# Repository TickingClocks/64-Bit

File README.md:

# 64-Bit
Nixie Tube Clock driven by an STM32F446. Drives 6 IN-12 Nixie Tubes

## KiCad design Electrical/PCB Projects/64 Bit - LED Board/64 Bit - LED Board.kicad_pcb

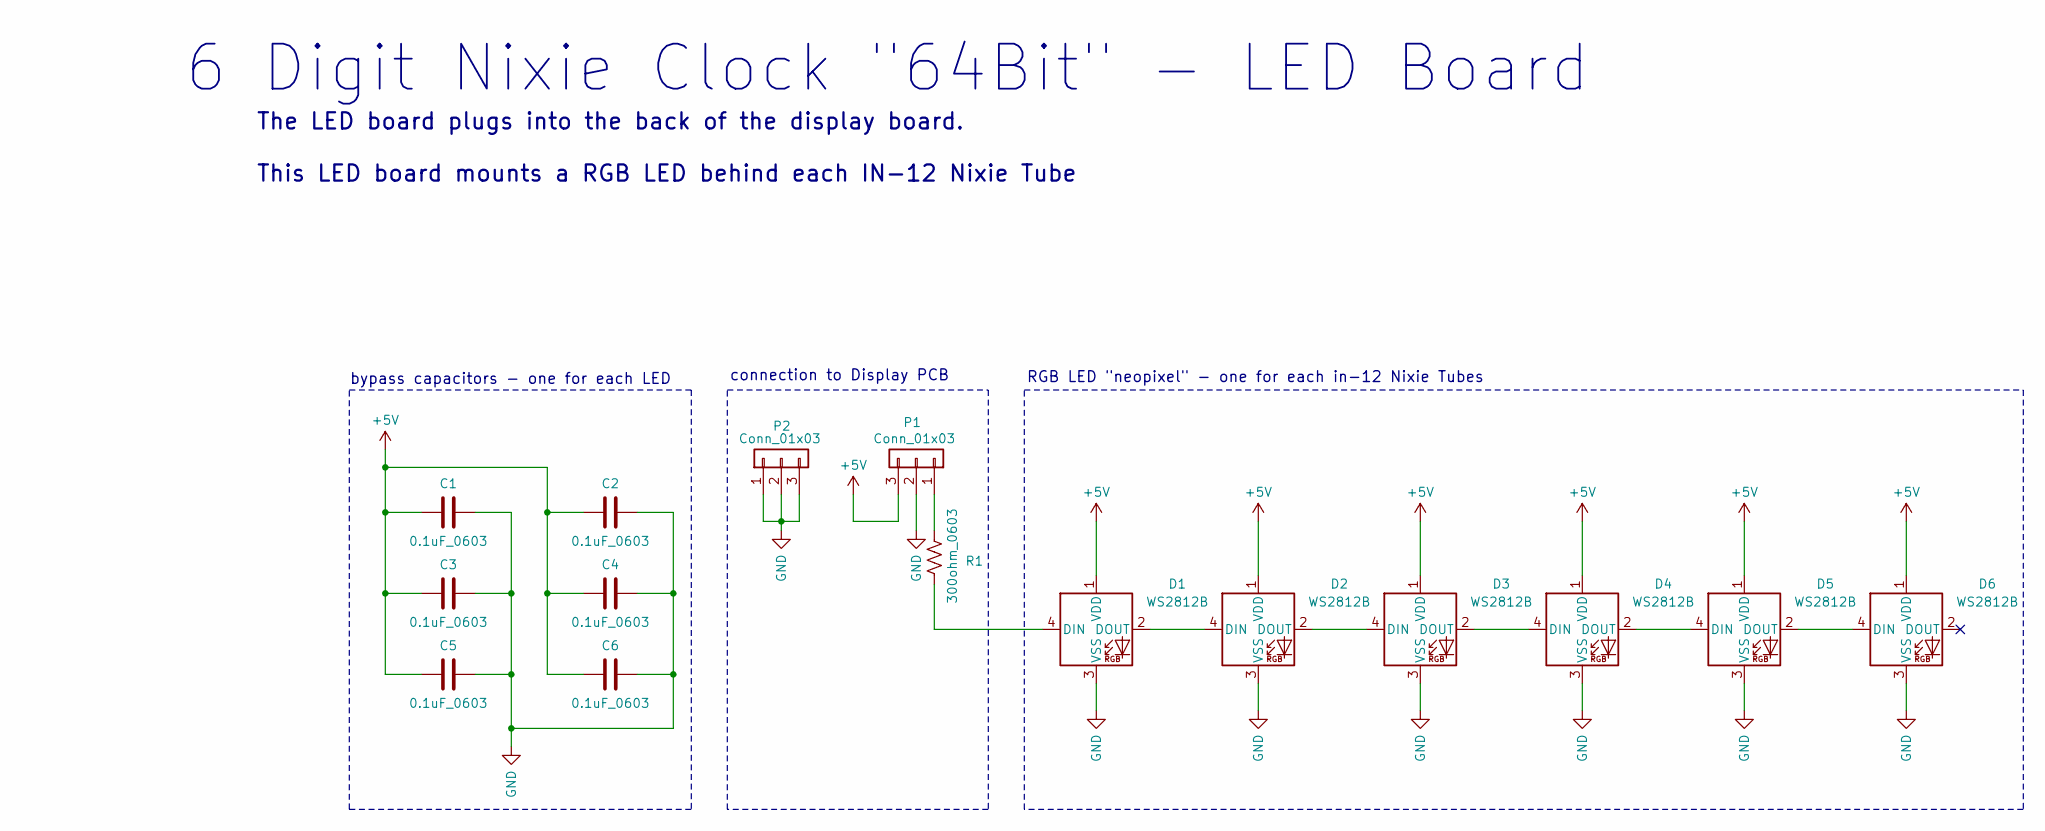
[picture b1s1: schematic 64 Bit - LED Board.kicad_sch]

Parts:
C1, C2, C3, C4, C5, C6: 0.1uF_0603; C_0603_1608Metric
D1, D2, D3, D4, D5, D6: WS2812B; LED_WS2812B_PLCC4_5.0x5.0mm_P3.2mm
P1, P2: Conn_01x03; PinHeader_1x03_P2.54mm_Vertical
R1: 300ohm_0603; R_0603_1608Metric

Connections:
+5V: C1.2, C2.2, C3.2, C4.2, C5.2, C6.2, D1.1 (VDD), D2.1 (VDD), D3.1 (VDD), D4.1 (VDD), D5.1 (VDD), D6.1 (VDD), P1.3
GND: C1.1, C2.1, C3.1, C4.1, C5.1, C6.1, D1.3 (VSS), D2.3 (VSS), D3.3 (VSS), D4.3 (VSS), D5.3 (VSS), D6.3 (VSS), P1.2, P2.1, P2.2, P2.3
unnamed: D1.4 (DIN), R1.2
unnamed: D1.2 (DOUT), D2.4 (DIN)
unnamed: D2.2 (DOUT), D3.4 (DIN)
unnamed: D3.2 (DOUT), D4.4 (DIN)
unnamed: D4.2 (DOUT), D5.4 (DIN)
unnamed: D5.2 (DOUT), D6.4 (DIN)
unnamed: P1.1, R1.1

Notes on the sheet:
connection to Display PCB
bypass capacitors - one for each LED
The LED board plugs into the back of the display board. This LED board mounts a RGB LED behind each IN-12 Nixie Tube
RGB LED "neopixel" - one for each in-12 Nixie Tubes
6 Digit Nixie Clock "64Bit" - LED Board

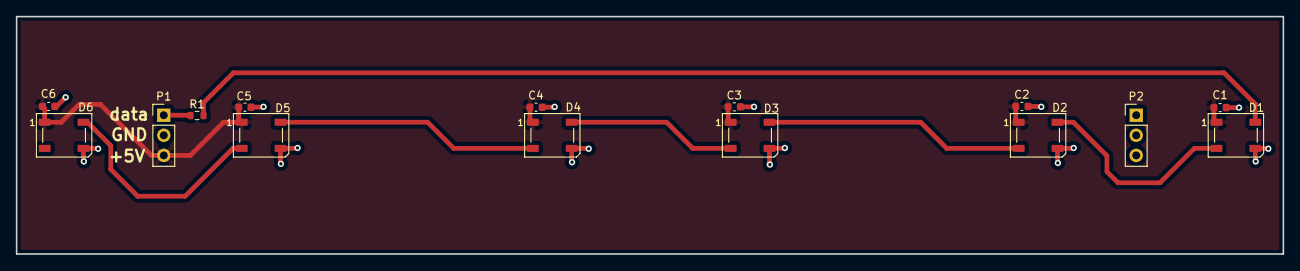
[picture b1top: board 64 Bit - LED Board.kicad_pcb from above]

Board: 2 copper layers, 160.1 x 30.0 mm, 15 parts (0 on the bottom side), 9 nets.

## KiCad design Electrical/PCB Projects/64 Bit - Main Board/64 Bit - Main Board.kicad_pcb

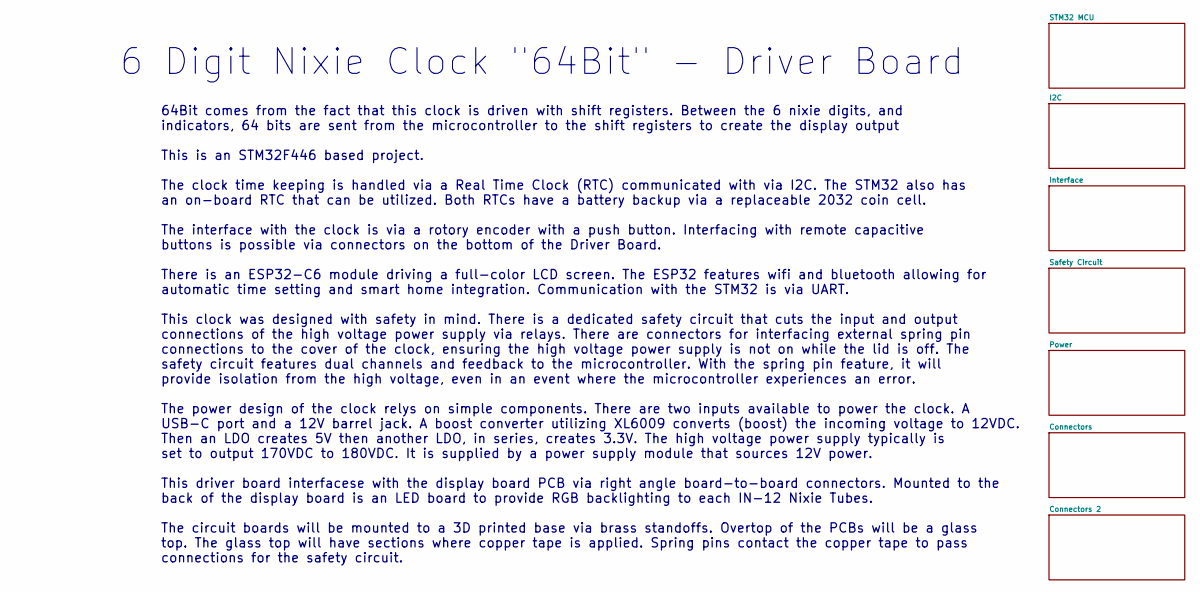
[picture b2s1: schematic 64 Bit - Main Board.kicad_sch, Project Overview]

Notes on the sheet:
64Bit comes from the fact that this clock is driven with shift registers. Between the 6 nixie digits, and indicators, 64 bits are sent from the microcontroller to the shift registers to create the display output This is an STM32F446 based project. The clock time keeping is handled via a Real Time C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
6 Digit Nixie Clock "64Bit" - Driver Board

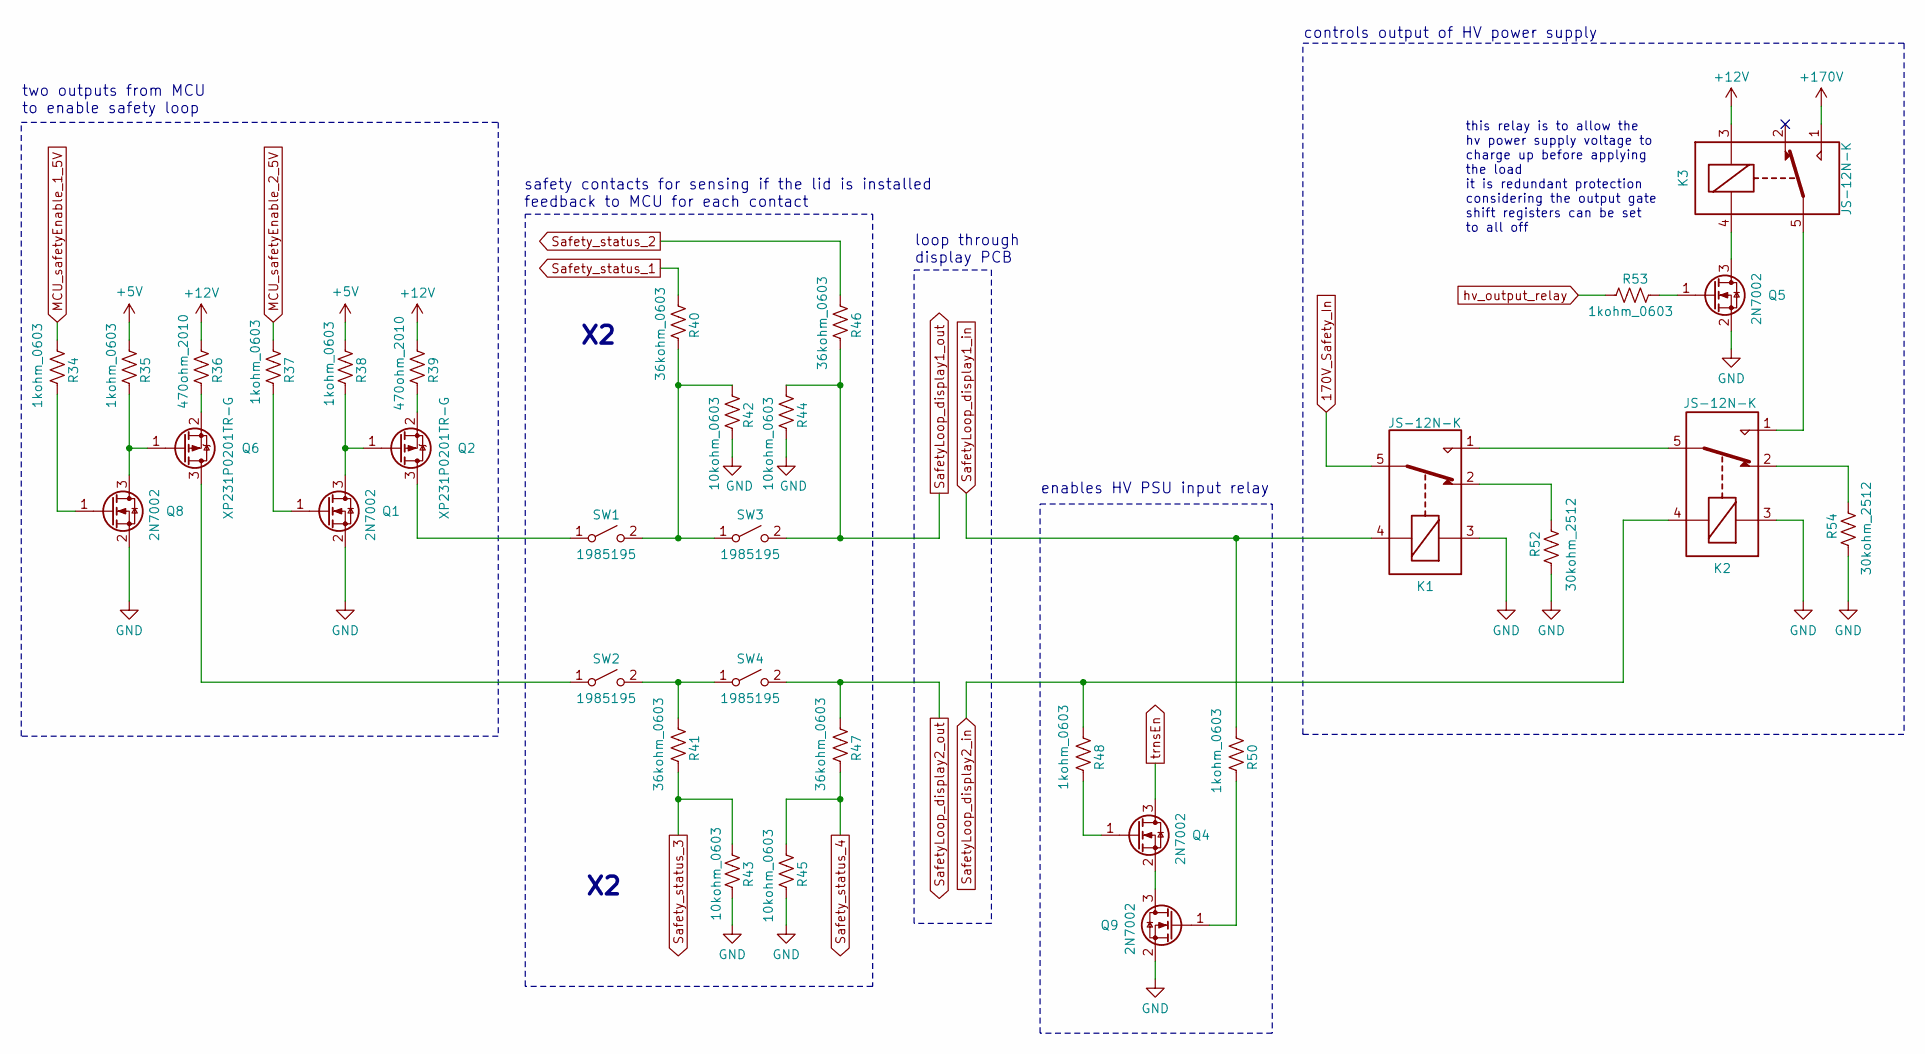
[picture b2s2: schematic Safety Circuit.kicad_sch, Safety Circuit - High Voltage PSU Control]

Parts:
K1, K2, K3: JS-12N-K
Q1, Q4, Q5, Q8, Q9: 2N7002; SOT-23
Q2, Q6: XP231P0201TR-G
R34, R35, R37, R38, R48, R50, R53: 1kohm_0603; R_0603_1608Metric
R36, R39: 470ohm_2010; R_2010_5025Metric
R40, R41, R46, R47: 36kohm_0603; R_0603_1608Metric
R42, R43, R44, R45: 10kohm_0603; R_0603_1608Metric
R52, R54: 30kohm_2512; R_2512_6332Metric
SW1, SW2, SW3, SW4: 1985195

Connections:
170V_Safety_In: K1.5; also elsewhere on the board
+5V: R35.2, R38.2; also elsewhere on the board
+12V: K3.3, R36.2, R39.2; also elsewhere on the board
+170V: K3.1; also elsewhere on the board
GND: K1.3, K2.3, Q1.2 (S), Q5.2 (S), Q8.2 (S), Q9.2 (S), R42.1, R43.1, R44.1, R45.1, R52.2, R54.2; also elsewhere on the board
MCU_safetyEnable_1_5V: R34.2; also elsewhere on the board
MCU_safetyEnable_2_5V: R37.2; also elsewhere on the board
unnamed: K1.1, K2.5
unnamed: K1.2, R52.1
unnamed: K2.1, K3.5
unnamed: K2.2, R54.1
unnamed: Q1.3 (D), Q2.1 (G), R38.1
unnamed: Q1.1 (G), R37.1
unnamed: Q2.3 (D), SW1.1 (A)
unnamed: Q2.2 (S), R39.1
unnamed: Q4.1 (G), R48.1
unnamed: Q4.2 (S), Q9.3 (D)
unnamed: K3.4, Q5.3 (D)
unnamed: Q5.1 (G), R53.1
unnamed: Q6.3 (D), SW2.1 (A)
unnamed: Q6.1 (G), Q8.3 (D), R35.1
unnamed: Q6.2 (S), R36.1
unnamed: Q8.1 (G), R34.1
unnamed: Q9.1 (G), R50.1
unnamed: R40.1, R42.2, SW1.2 (B), SW3.1 (A)
unnamed: R41.2, SW2.2 (B), SW4.1 (A)
SafetyLoop_display1_in: K1.4, R50.2; also elsewhere on the board
SafetyLoop_display1_out: R44.2, R46.1, SW3.2 (B); also elsewhere on the board
SafetyLoop_display2_in: K2.4, R48.2; also elsewhere on the board
SafetyLoop_display2_out: R47.2, SW4.2 (B); also elsewhere on the board
Safety_status_1: R40.2; also elsewhere on the board
Safety_status_2: R46.2; also elsewhere on the board
Safety_status_3: R41.1, R43.2; also elsewhere on the board
Safety_status_4: R45.2, R47.1; also elsewhere on the board
hv_output_relay: R53.2; also elsewhere on the board
trnsEn: Q4.3 (D); also elsewhere on the board

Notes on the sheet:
controls output of HV power supply
enables HV PSU input relay
loop through display PCB
this relay is to allow the hv power supply voltage to charge up before applying the load it is redundant protection considering the output gate shift registers can be set to all off
safety contacts for sensing if the lid is installed feedback to MCU for each contact
two outputs from MCU to enable safety loop

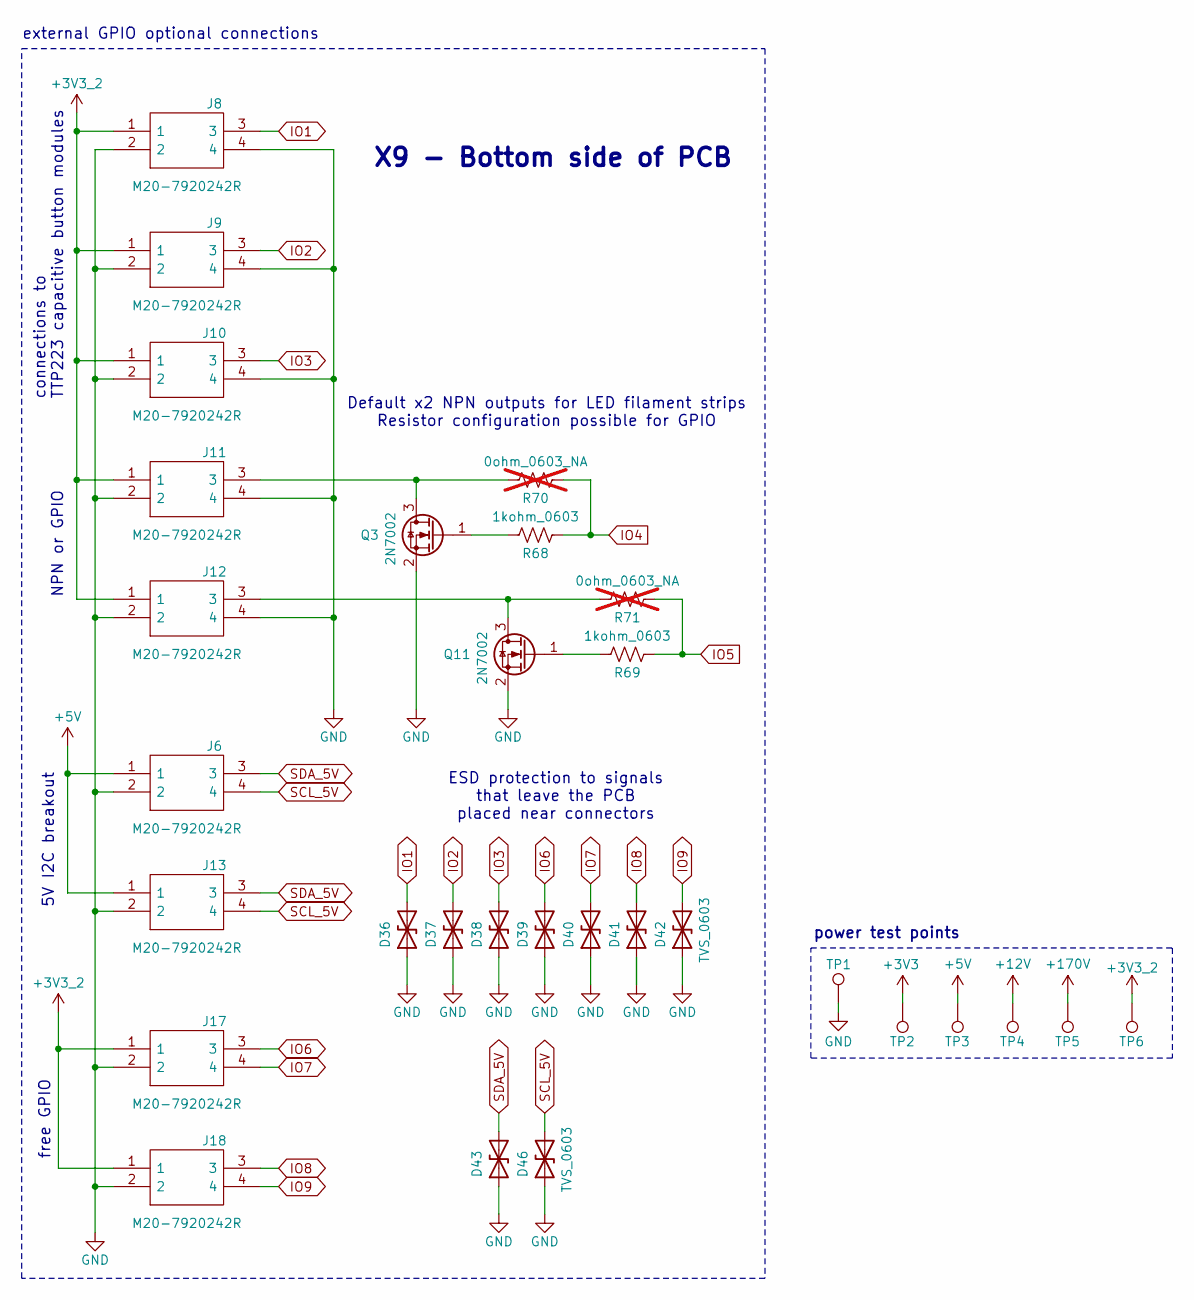
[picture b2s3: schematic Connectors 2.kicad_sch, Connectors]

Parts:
D36, D37, D38, D39, D40, D41, D42, D43, D46: TVS_0603; R_0603_1608Metric
J6, J8, J9, J10, J11, J12, J13, J17, J18: M20-7920242R; M207920242R; Mouser Part Number 855-M20-7920242R
Q3, Q11: 2N7002; SOT-23
R68, R69: 1kohm_0603; R_0603_1608Metric
R70, R71: 0ohm_0603_NA; R_0603_1608Metric; not fitted
TP1, TP2, TP3, TP4, TP5, TP6: TestPoint; TestPoint_THTPad_D1.5mm_Drill0.7mm

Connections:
+3V3: TP2.1; also elsewhere on the board
+3V3_2: J8.1, J9.1, J10.1, J11.1, J12.1, J17.1, J18.1, TP6.1; also elsewhere on the board
+5V: J6.1, J13.1, TP3.1; also elsewhere on the board
+12V: TP4.1; also elsewhere on the board
+170V: TP5.1; also elsewhere on the board
GND: D36.1 (A1), D37.1 (A1), D38.1 (A1), D39.1 (A1), D40.1 (A1), D41.1 (A1), D42.1 (A1), D43.1 (A1), D46.1 (A1), J6.2, J8.2, J8.4, J9.2, J9.4, J10.2, J10.4, J11.2, J11.4, J12.2, J12.4, J13.2, J17.2, J18.2, Q3.2 (S), Q11.2 (S), TP1.1; also elsewhere on the board
IO1: D36.2 (A2), J8.3; also elsewhere on the board
IO2: D37.2 (A2), J9.3; also elsewhere on the board
IO3: D38.2 (A2), J10.3; also elsewhere on the board
IO4: R68.1, R70.1; also elsewhere on the board
IO5: R69.1, R71.1; also elsewhere on the board
IO6: D39.2 (A2), J17.3; also elsewhere on the board
IO7: D40.2 (A2), J17.4; also elsewhere on the board
IO8: D41.2 (A2), J18.3; also elsewhere on the board
IO9: D42.2 (A2), J18.4; also elsewhere on the board
unnamed: J11.3, Q3.3 (D), R70.2
unnamed: Q3.1 (G), R68.2
unnamed: J12.3, Q11.3 (D), R71.2
unnamed: Q11.1 (G), R69.2
SCL_5V: D46.2 (A2), J6.4, J13.4; also elsewhere on the board
SDA_5V: D43.2 (A2), J6.3, J13.3; also elsewhere on the board

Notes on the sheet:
external GPIO optional connections
5V I2C breakout
ESD protection to signals that leave the PCB placed near connectors
NPN or GPIO
X9 - Bottom side of PCB
power test points
free GPIO
Default x2 NPN outputs for LED filament strips Resistor configuration possible for GPIO
connections to TTP223 capacitive button modules

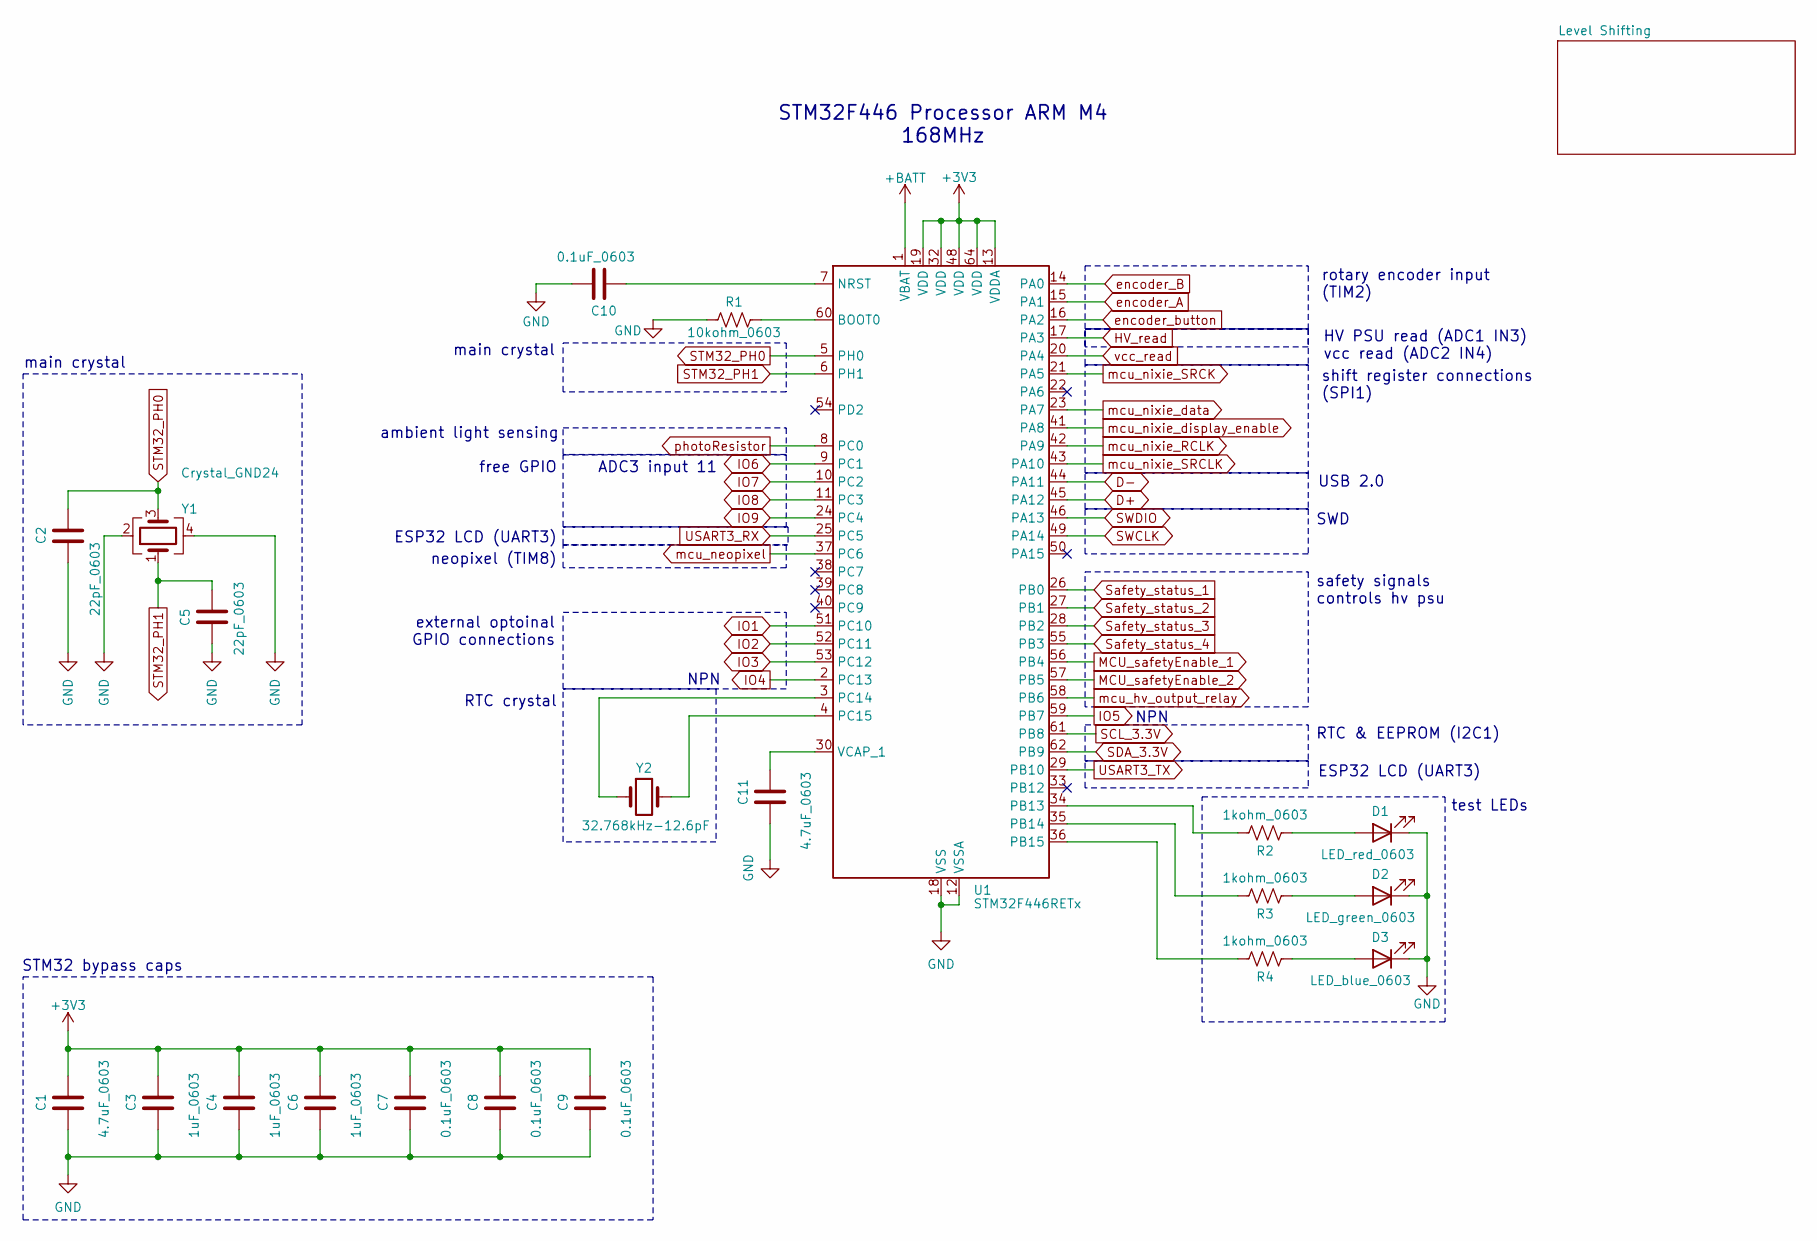
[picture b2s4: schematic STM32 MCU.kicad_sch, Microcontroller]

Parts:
C1, C11: 4.7uF_0603; C_0603_1608Metric
C2, C5: 22pF_0603; C_0603_1608Metric
C3, C4, C6: 1uF_0603; C_0603_1608Metric
C7, C8, C9, C10: 0.1uF_0603; C_0603_1608Metric
D1: LED_red_0603; LED_0603_1608Metric
D2: LED_green_0603; LED_0603_1608Metric
D3: LED_blue_0603; LED_0603_1608Metric
R1: 10kohm_0603; R_0603_1608Metric
R2, R3, R4: 1kohm_0603; R_0603_1608Metric
U1: STM32F446RETx; LQFP-64_10x10mm_P0.5mm
Y1: Crystal_GND24; ECS1602033TR3
Y2: 32.768kHz-12.6pF; 37.768kHz

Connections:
+3V3: C1.1, C3.1, C4.1, C6.1, C7.1, C8.1, C9.1, U1.13 (VDDA), U1.19 (VDD), U1.32 (VDD), U1.48 (VDD), U1.64 (VDD); also elsewhere on the board
+BATT: U1.1 (VBAT); also elsewhere on the board
D+: U1.45 (PA12); also elsewhere on the board
D-: U1.44 (PA11); also elsewhere on the board
GND: C1.2, C2.2, C3.2, C4.2, C5.1, C6.2, C7.2, C8.2, C9.2, C10.2, C11.2, D1.1 (K), D2.1 (K), D3.1 (K), R1.1, U1.12 (VSSA), U1.18 (VSS), U1.31 (VSS), U1.47 (VSS), U1.63 (VSS), Y1.2, Y1.4; also elsewhere on the board
HV_read: U1.17 (PA3); also elsewhere on the board
IO1: U1.51 (PC10); also elsewhere on the board
IO2: U1.52 (PC11); also elsewhere on the board
IO3: U1.53 (PC12); also elsewhere on the board
IO4: U1.2 (PC13); also elsewhere on the board
IO5: U1.59 (PB7); also elsewhere on the board
IO6: U1.9 (PC1); also elsewhere on the board
IO7: U1.10 (PC2); also elsewhere on the board
IO8: U1.11 (PC3); also elsewhere on the board
IO9: U1.24 (PC4); also elsewhere on the board
MCU_safetyEnable_1: U1.56 (PB4); also elsewhere on the board
MCU_safetyEnable_2: U1.57 (PB5); also elsewhere on the board
unnamed: D1.2 (A), R2.1
unnamed: D2.2 (A), R3.1
unnamed: D3.2 (A), R4.1
unnamed: R1.2, U1.60 (BOOT0)
unnamed: C10.1, U1.7 (NRST)
unnamed: R2.2, U1.34 (PB13)
unnamed: R3.2, U1.35 (PB14)
unnamed: R4.2, U1.36 (PB15)
unnamed: U1.3 (PC14), Y2.1
unnamed: U1.4 (PC15), Y2.2
unnamed: C11.1, U1.30 (VCAP_1)
SCL_3.3V: U1.61 (PB8); also elsewhere on the board
SDA_3.3V: U1.62 (PB9); also elsewhere on the board
STM32_PH0: C2.1, U1.5 (PH0), Y1.3
STM32_PH1: C5.2, U1.6 (PH1), Y1.1
SWCLK: U1.49 (PA14); also elsewhere on the board
SWDIO: U1.46 (PA13); also elsewhere on the board
Safety_status_1: U1.26 (PB0); also elsewhere on the board
Safety_status_2: U1.27 (PB1); also elsewhere on the board
Safety_status_3: U1.28 (PB2); also elsewhere on the board
Safety_status_4: U1.55 (PB3); also elsewhere on the board
USART3_RX: U1.25 (PC5); also elsewhere on the board
USART3_TX: U1.29 (PB10); also elsewhere on the board
encoder_A: U1.15 (PA1); also elsewhere on the board
encoder_B: U1.14 (PA0); also elsewhere on the board
encoder_button: U1.16 (PA2); also elsewhere on the board
mcu_hv_output_relay: U1.58 (PB6); also elsewhere on the board
mcu_neopixel: U1.37 (PC6); also elsewhere on the board
mcu_nixie_RCLK: U1.42 (PA9); also elsewhere on the board
mcu_nixie_SRCK: U1.21 (PA5); also elsewhere on the board
mcu_nixie_SRCLK: U1.43 (PA10); also elsewhere on the board
mcu_nixie_data: U1.23 (PA7); also elsewhere on the board
mcu_nixie_display_enable: U1.41 (PA8); also elsewhere on the board
photoResistor: U1.8 (PC0); also elsewhere on the board
vcc_read: U1.20 (PA4); also elsewhere on the board

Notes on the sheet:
HV PSU read (ADC1 IN3) vcc read (ADC2 IN4)
free GPIO
ESP32 LCD (UART3)
SWD
STM32 bypass caps
rotary encoder input (TIM2)
RTC & EEPROM (I2C1)
NPN
USB 2.0
external optoinal GPIO connections
test LEDs
ADC3 input 11
neopixel (TIM8)
safety signals controls hv psu
STM32F446 Processor ARM M4 168MHz
RTC crystal
shift register connections (SPI1)
ambient light sensing
main crystal

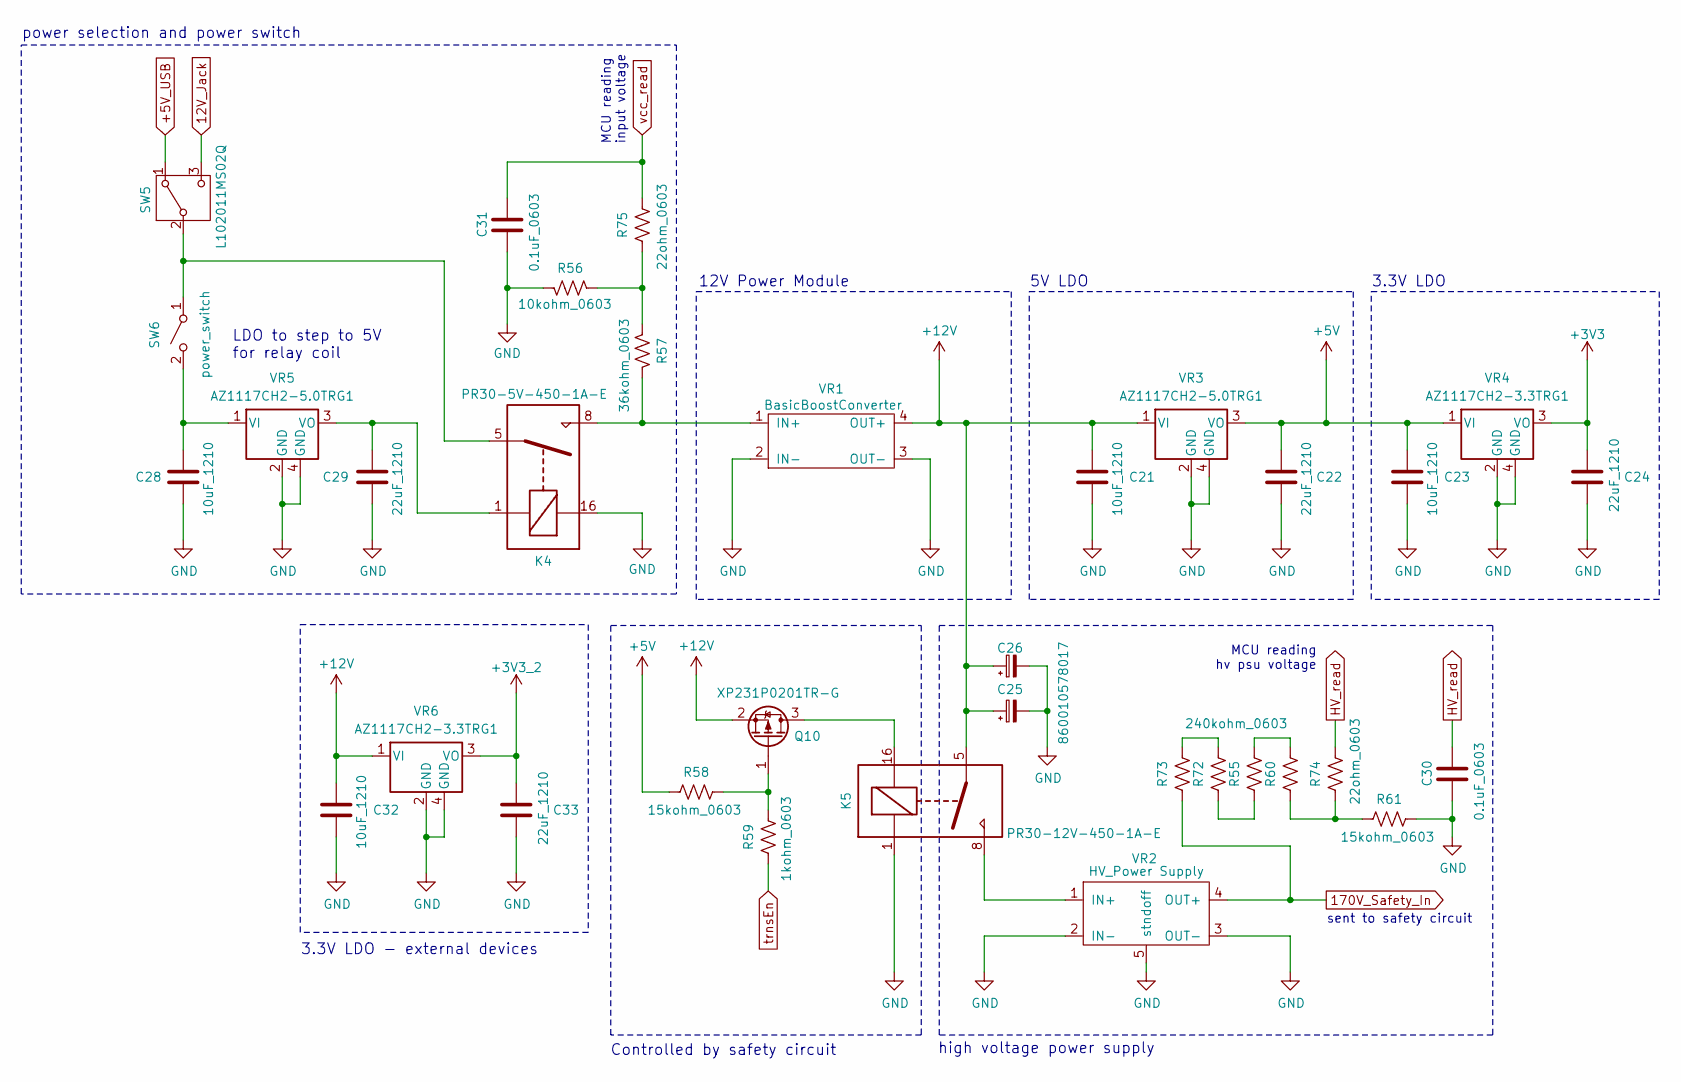
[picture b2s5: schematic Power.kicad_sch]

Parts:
C21, C23, C28, C32: 10uF_1210; C_1210_3225Metric
C22, C24, C29, C33: 22uF_1210; C_1210_3225Metric
C25, C26: 860010578017; CP_Radial_D13.0mm_P5.00mm
C30, C31: 0.1uF_0603; C_0603_1608Metric
K4: PR30-5V-450-1A-E; PR30-12V-450-1A-E
K5: PR30-12V-450-1A-E
Q10: XP231P0201TR-G
R55, R60, R72, R73: 240kohm_0603; R_0603_1608Metric
R56: 10kohm_0603; R_0603_1608Metric
R57: 36kohm_0603; R_0603_1608Metric
R58, R61: 15kohm_0603; R_0603_1608Metric
R59: 1kohm_0603; R_0603_1608Metric
R74, R75: 22ohm_0603; R_0603_1608Metric
SW5: L102011MS02Q
SW6: power_switch; 1985195
VR1: BasicBoostConverter; XL6009_Module(43mmx21mm)
VR2: HV_Power Supply; hv_psu
VR3, VR5: AZ1117CH2-5.0TRG1
VR4, VR6: AZ1117CH2-3.3TRG1

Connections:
12V_Jack: SW5.3 (C); also elsewhere on the board
170V_Safety_In: R73.1, VR2.4 (OUT+); also elsewhere on the board
+3V3: C24.1, VR4.3 (VO); also elsewhere on the board
+3V3_2: C33.1, VR6.3 (VO); also elsewhere on the board
+5V: C22.1, C23.1, R58.1, VR3.3 (VO), VR4.1 (VI); also elsewhere on the board
+5V_USB: SW5.1 (A); also elsewhere on the board
+12V: C21.1, C25.1, C26.1, C32.1, K5.5, Q10.2 (S), VR1.4 (OUT+), VR3.1 (VI), VR6.1 (VI); also elsewhere on the board
GND: C21.2, C22.2, C23.2, C24.2, C25.2, C26.2, C28.2, C29.2, C30.1, C31.1, C32.2, C33.2, K4.16, K5.1, R56.2, R61.2, VR1.2 (IN-), VR1.3 (OUT-), VR2.2 (IN-), VR2.3 (OUT-), VR2.5 (stndoff), VR3.2 (GND), VR3.4 (GND), VR4.2 (GND), VR4.4 (GND), VR5.2 (GND), VR5.4 (GND), VR6.2 (GND), VR6.4 (GND); also elsewhere on the board
HV_read: C30.2, R74.2; also elsewhere on the board
unnamed: K5.16, Q10.3 (D)
unnamed: Q10.1 (G), R58.2, R59.2
unnamed: R55.1, R72.1
unnamed: R55.2, R60.2
unnamed: R56.1, R57.2, R75.1
unnamed: R60.1, R61.1, R74.1
unnamed: R72.2, R73.2
unnamed: K4.5, SW5.2 (B), SW6.1 (A)
unnamed: C28.1, SW6.2 (B), VR5.1 (VI)
unnamed: K4.8, R57.1, VR1.1 (IN+)
unnamed: K5.8, VR2.1 (IN+)
unnamed: C29.1, K4.1, VR5.3 (VO)
trnsEn: R59.1; also elsewhere on the board
vcc_read: C31.2, R75.2; also elsewhere on the board

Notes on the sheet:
MCU reading input voltage
high voltage power supply
Controlled by safety circuit
5V LDO
sent to safety circuit
LDO to step to 5V for relay coil
3.3V LDO - external devices
12V Power Module
MCU reading hv psu voltage
power selection and power switch
3.3V LDO

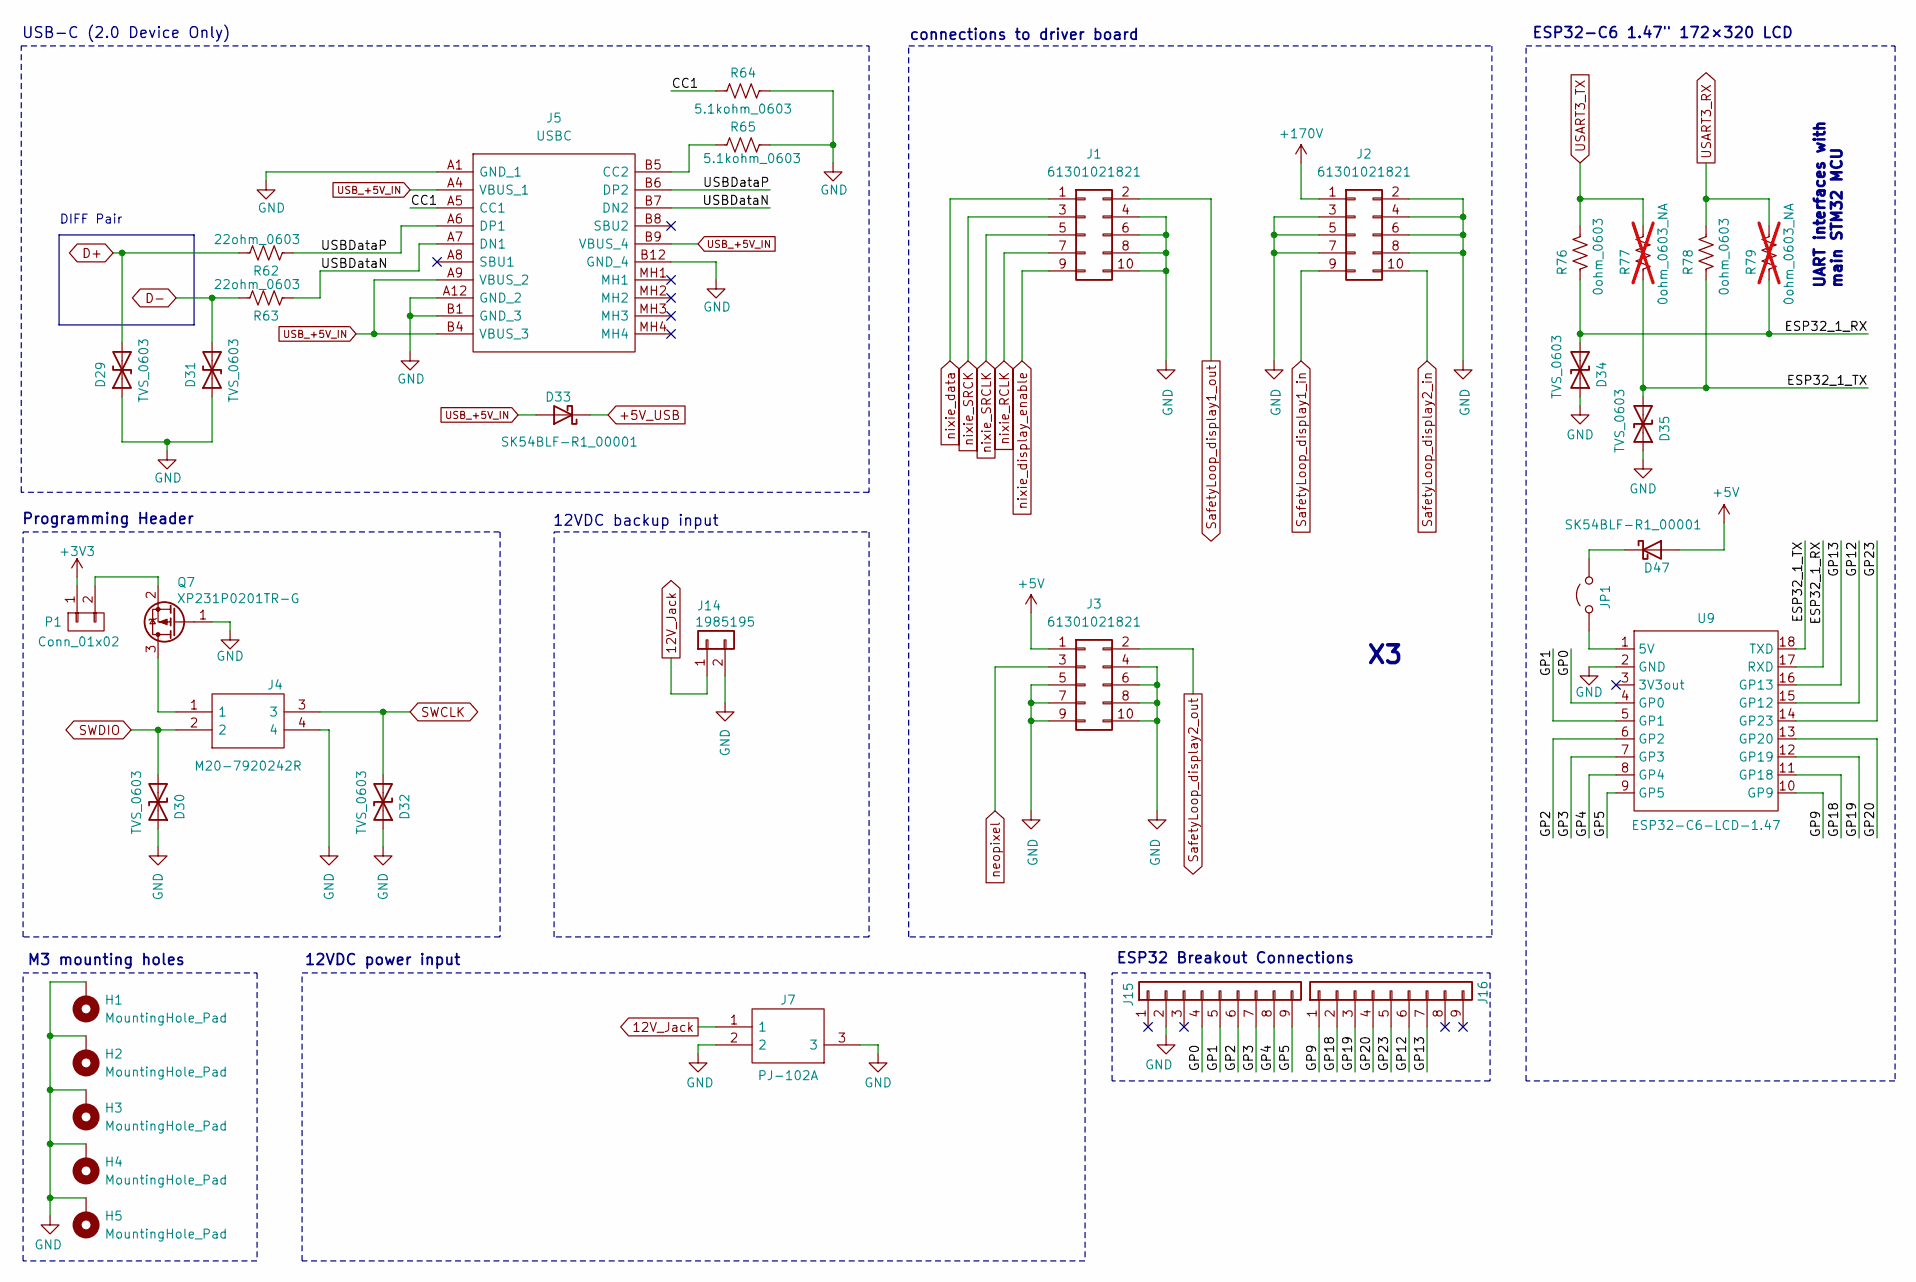
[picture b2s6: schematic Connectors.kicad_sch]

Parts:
D29, D30, D31, D32, D34, D35: TVS_0603; R_0603_1608Metric
D33, D47: SK54BLF-R1_00001
H1, H2, H3, H4, H5: MountingHole_Pad; M3 Standoff Footprint
J1, J2, J3: 61301021821
J4: M20-7920242R; M207920242R; Mouser Part Number 855-M20-7920242R
J5: USBC; USB421603A
J7: PJ-102A; PJ-102AH; Mouser Part Number 490-PJ-102A
J14: 1985195
J15, J16: Conn_01x09; PinSocket_1x09_P2.54mm_Vertical
JP1: Jumper_2_Open; PinHeader_1x02_P2.54mm_Vertical
P1: Conn_01x02; PinHeader_1x02_P2.54mm_Vertical
Q7: XP231P0201TR-G
R62, R63: 22ohm_0603; R_0603_1608Metric
R64, R65: 5.1kohm_0603; R_0603_1608Metric
R76, R78: 0ohm_0603; R_0603_1608Metric
R77, R79: 0ohm_0603_NA; R_0603_1608Metric; not fitted
U9: ESP32-C6-LCD-1.47

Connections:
12V_Jack: J7.1, J14.1; also elsewhere on the board
+3V3: P1.1; also elsewhere on the board
+5V: D47.2 (A), J3.1; also elsewhere on the board
+5V_USB: D33.1 (K); also elsewhere on the board
+170V: J2.1; also elsewhere on the board
/Connectors/CC1: J5.A5 (CC1), R64.2
/Connectors/ESP32_1_RX: D34.2 (A2), R76.1, R79.1, U9.17 (RXD)
/Connectors/ESP32_1_TX: D35.2 (A2), R77.1, R78.1, U9.18 (TXD)
/Connectors/GP0: J15.4, U9.4 (GP0)
/Connectors/GP1: J15.5, U9.5 (GP1)
/Connectors/GP2: J15.6, U9.6 (GP2)
/Connectors/GP3: J15.7, U9.7 (GP3)
/Connectors/GP4: J15.8, U9.8 (GP4)
/Connectors/GP5: J15.9, U9.9 (GP5)
/Connectors/GP9: J16.1, U9.10 (GP9)
/Connectors/GP12: J16.6, U9.15 (GP12)
/Connectors/GP13: J16.7, U9.16 (GP13)
/Connectors/GP18: J16.2, U9.11 (GP18)
/Connectors/GP19: J16.3, U9.12 (GP19)
/Connectors/GP20: J16.4, U9.13 (GP20)
/Connectors/GP23: J16.5, U9.14 (GP23)
/Connectors/USBDataN: J5.A7 (DN1), J5.B7 (DN2), R63.1
/Connectors/USBDataP: J5.A6 (DP1), J5.B6 (DP2), R62.1
D+: D29.2 (A2), R62.2; also elsewhere on the board
D-: D31.2 (A2), R63.2; also elsewhere on the board
GND: D29.1 (A1), D30.1 (A1), D31.1 (A1), D32.1 (A1), D34.1 (A1), D35.1 (A1), H1.1, H2.1, H3.1, H4.1, H5.1, J1.4, J1.6, J1.8, J1.10, J2.2, J2.3, J2.4, J2.5, J2.6, J2.7, J2.8, J3.4, J3.5, J3.6, J3.7, J3.8, J3.9, J3.10, J4.4, J5.A1 (GND_1), J5.A12 (GND_2), J5.B1 (GND_3), J5.B12 (GND_4), J7.2, J7.3, J14.2, J15.2, Q7.1 (G), R64.1, R65.2, U9.2 (GND); also elsewhere on the board
unnamed: D47.1 (K), JP1.2 (B)
unnamed: J5.B5 (CC2), R65.1
unnamed: JP1.1 (A), U9.1 (5V)
unnamed: P1.2, Q7.2 (S)
unnamed: J4.1, Q7.3 (D)
SWCLK: D32.2 (A2), J4.3; also elsewhere on the board
SWDIO: D30.2 (A2), J4.2; also elsewhere on the board
SafetyLoop_display1_in: J2.9; also elsewhere on the board
SafetyLoop_display1_out: J1.2; also elsewhere on the board
SafetyLoop_display2_in: J2.10; also elsewhere on the board
SafetyLoop_display2_out: J3.2; also elsewhere on the board
USART3_RX: R78.2, R79.2; also elsewhere on the board
USART3_TX: R76.2, R77.2; also elsewhere on the board
USB_+5V_IN: D33.2 (A), J5.A4 (VBUS_1), J5.A9 (VBUS_2), J5.B4 (VBUS_3), J5.B9 (VBUS_4)
neopixel: J3.3; also elsewhere on the board
nixie_RCLK: J1.7; also elsewhere on the board
nixie_SRCK: J1.3; also elsewhere on the board
nixie_SRCLK: J1.5; also elsewhere on the board
nixie_data: J1.1; also elsewhere on the board
nixie_display_enable: J1.9; also elsewhere on the board

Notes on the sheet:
Programming Header
ESP32-C6 1.47" 172×320 LCD
M3 mounting holes
DIFF Pair
connections to driver board
ESP32 Breakout Connections
UART interfaces with main STM32 MCU
12VDC power input
12VDC backup input
USB-C (2.0 Device Only)
